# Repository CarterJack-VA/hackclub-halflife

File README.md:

# hackclub-halflife
## Projects - 
### Starbie - Week 1
<details>
 <summary>
[PCB](https://github.com/CarterJack-VA/hackclub-halflife/blob/main/hl-project1.kicad_pcb)
  </summary>
  
 </details>
<details><summary>[Schematic](https://github.com/CarterJack-VA/hackclub-halflife/blob/main/hl-project1.kicad_sch)</summary>

</details>

[Firmware](https://github.com/CarterJack-VA/hackclub-halflife/blob/main/firmware/firmware.ino)

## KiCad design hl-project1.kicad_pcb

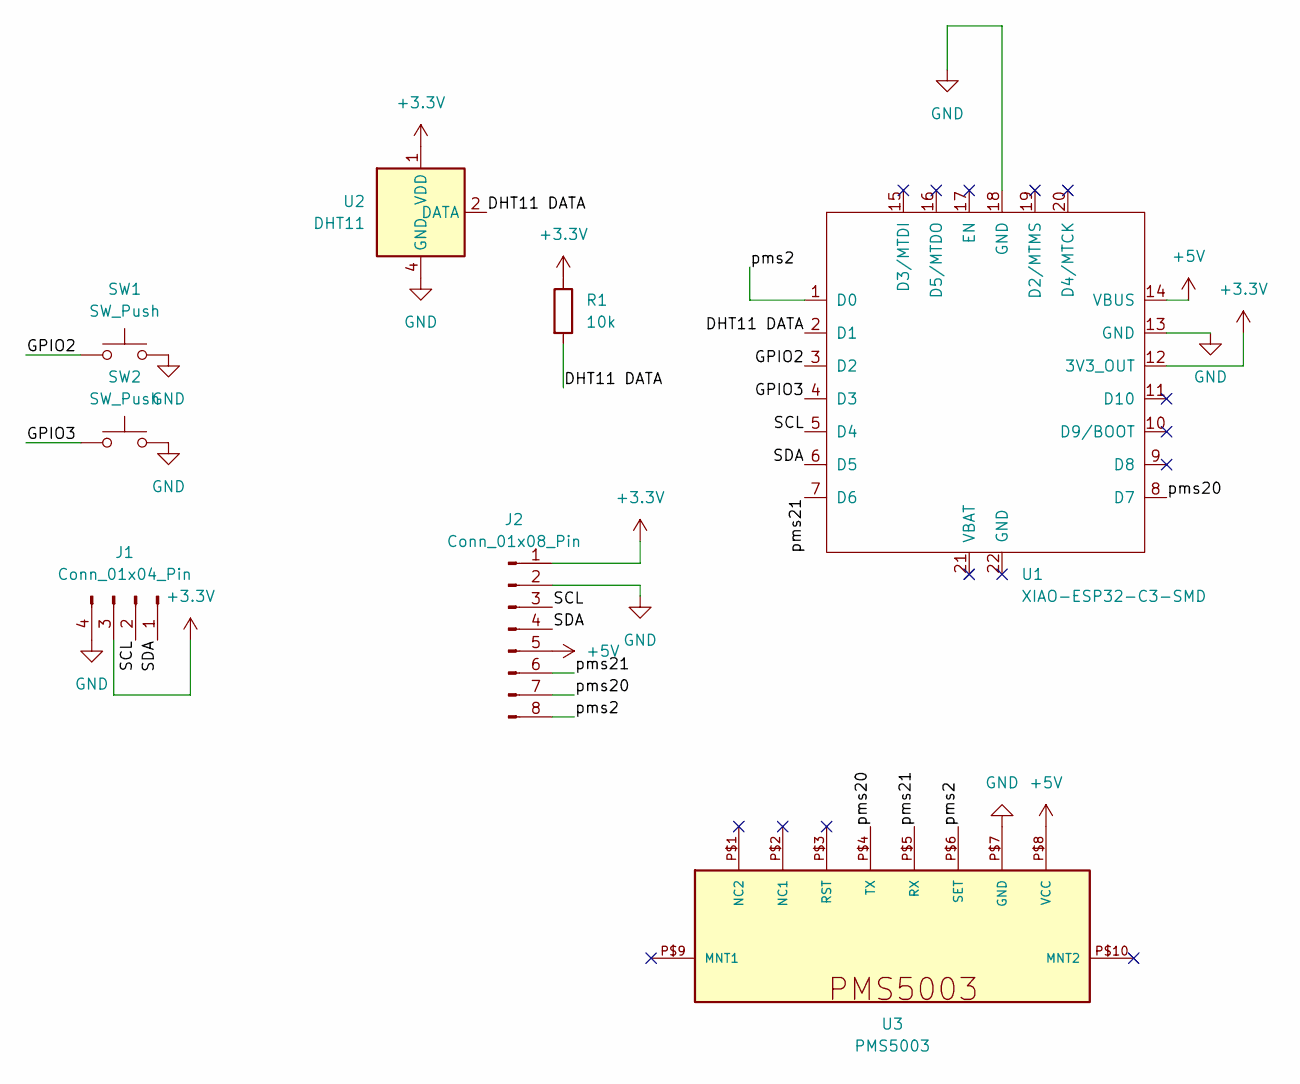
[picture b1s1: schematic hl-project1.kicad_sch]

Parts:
J1: Conn_01x04_Pin; Display_128x64_096_I2C
J2: Conn_01x08_Pin; PinHeader_1x08_P2.54mm_Vertical
R1: 10k; R_Axial_DIN0204_L3.6mm_D1.6mm_P7.62mm_Horizontal
SW1, SW2: SW_Push; SW_Cherry_MX_1.00u_PCB
U1: XIAO-ESP32-C3-SMD
U2: DHT11; Aosong_DHT11_5.5x12.0_P2.54mm
U3: PMS5003

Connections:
+3.3V: J1.3, J2.1, R1.1, U1.12 (3V3_OUT), U2.1 (VDD)
+5V: J2.5, U1.14 (VBUS), U3.P$8 (VCC)
/DHT11 DATA: R1.2, U1.2 (D1), U2.2 (DATA)
/GPIO2: SW1.1, U1.3 (D2)
/GPIO3: SW2.1, U1.4 (D3)
/SCL: J1.2, J2.3, U1.5 (D4)
/SDA: J1.1, J2.4, U1.6 (D5)
/pms2: J2.8, U1.1 (D0), U3.P$6 (SET)
/pms20: J2.7, U1.8 (D7), U3.P$4 (TX)
/pms21: J2.6, U1.7 (D6), U3.P$5 (RX)
GND: J1.4, J2.2, SW1.2, SW2.2, U1.13 (GND), U1.18 (GND), U2.4 (GND), U3.P$7 (GND)

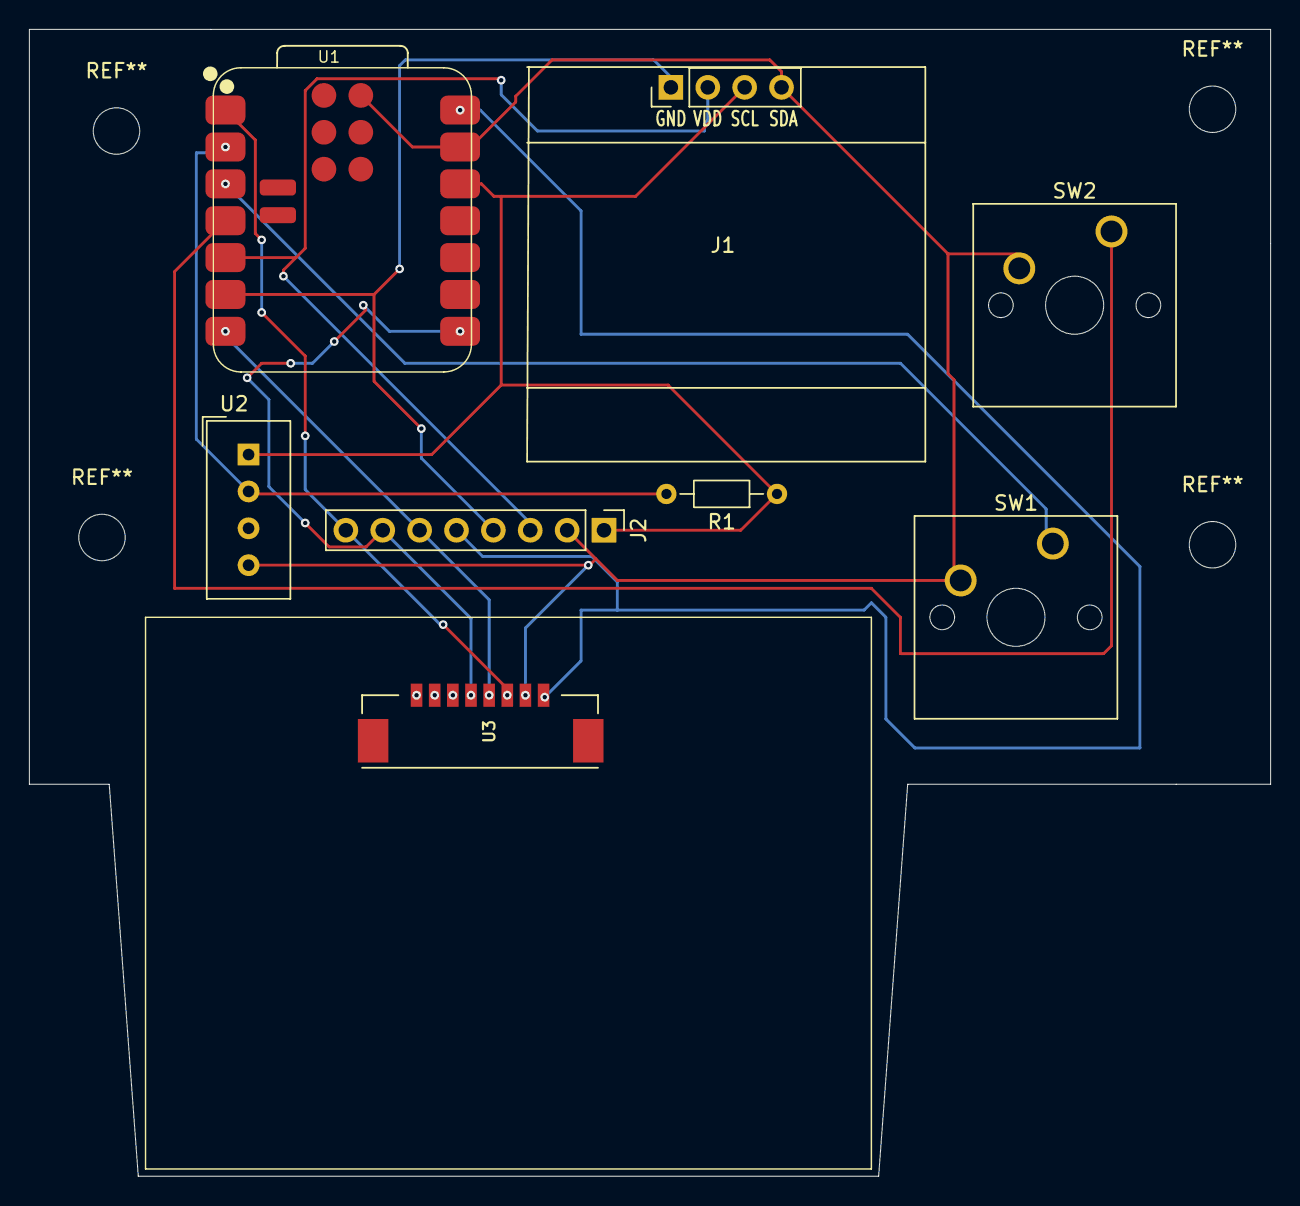
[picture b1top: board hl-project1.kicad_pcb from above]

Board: 2 copper layers, 85.5 x 79.0 mm, 8 parts (0 on the bottom side), 11 nets.
